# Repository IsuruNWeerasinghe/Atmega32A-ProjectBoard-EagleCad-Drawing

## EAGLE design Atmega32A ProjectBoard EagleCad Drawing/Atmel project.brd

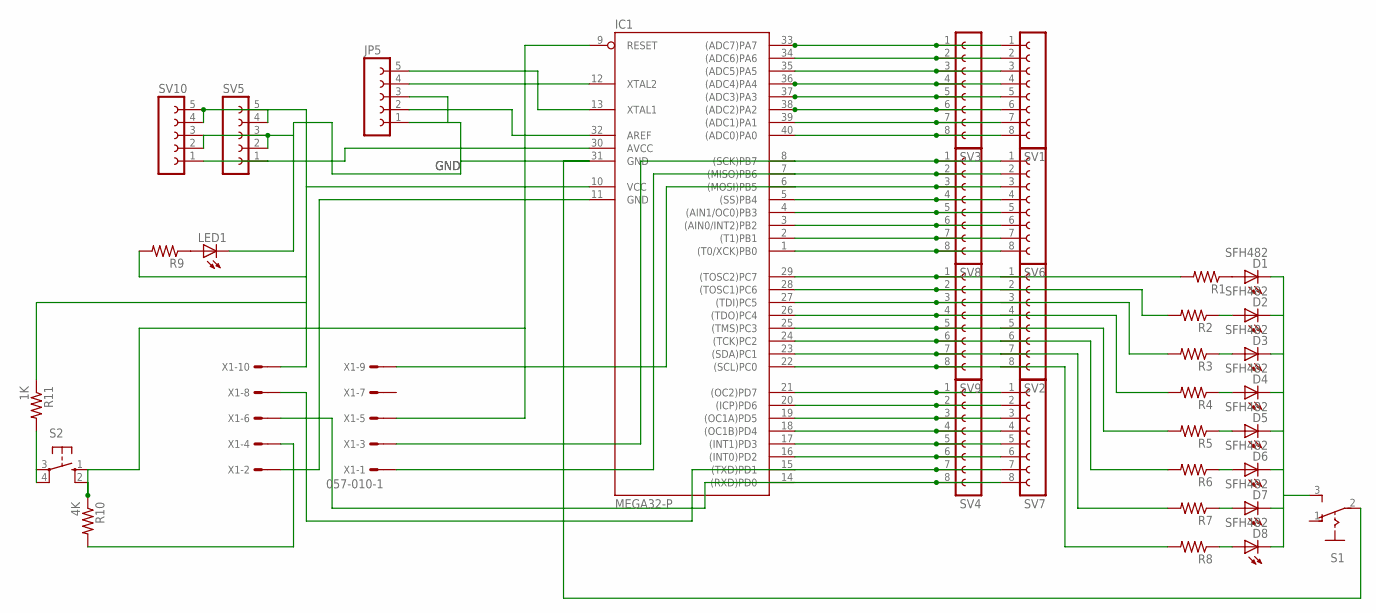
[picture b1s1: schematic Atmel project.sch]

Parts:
D1, D2, D3, D4, D5, D6, D7, D8: SFH482
IC1: MEGA32-P; DIL40
JP5: FE05-1
LED1: LED3MM
R1, R2, R3, R4, R5, R6, R7, R8, R9: R-US_0204/7; 0204/7
R10: 4K; 0204/7
R11: 1K; 0204/7
S1: 255SB
S2: 10-XX; B3F-10XX
SV1, SV2, SV3, SV4, SV6, SV7, SV8, SV9: FE08-1; FE08
SV5, SV10: FE05-1
X1: 057-010-1

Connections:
GND: IC1.11 (GND), IC1.31 (GND), JP5.1, JP5.3, LED1.K (C), R10.2, S1.2, SV5.2, SV5.3, SV10.2, SV10.3, X1.2, X1.4
unnamed: IC1.40 ((ADC0)PA0), SV1.8, SV3.8
unnamed: IC1.39 ((ADC1)PA1), SV1.7, SV3.7
unnamed: IC1.38 ((ADC2)PA2), SV1.6, SV3.6
unnamed: IC1.37 ((ADC3)PA3), SV1.5, SV3.5
unnamed: IC1.36 ((ADC4)PA4), SV1.4, SV3.4
unnamed: IC1.35 ((ADC5)PA5), SV1.3, SV3.3
unnamed: IC1.34 ((ADC6)PA6), SV1.2, SV3.2
unnamed: IC1.33 ((ADC7)PA7), SV1.1, SV3.1
unnamed: IC1.8 ((SCK)PB7), SV6.1, SV8.1, X1.3
unnamed: IC1.7 ((MISO)PB6), SV6.2, SV8.2, X1.1
unnamed: IC1.12 (XTAL2), JP5.4
unnamed: IC1.5 ((SS)PB4), SV6.4, SV8.4
unnamed: IC1.4 ((AIN1/OC0)PB3), SV6.5, SV8.5
unnamed: IC1.3 ((AIN0/INT2)PB2), SV6.6, SV8.6
unnamed: IC1.2 ((T1)PB1), SV6.7, SV8.7
unnamed: IC1.1 ((T0/XCK)PB0), SV6.8, SV8.8
unnamed: IC1.29 ((TOSC2)PC7), R1.2, SV2.1, SV9.1
unnamed: IC1.28 ((TOSC1)PC6), R2.2, SV2.2, SV9.2
unnamed: IC1.27 ((TDI)PC5), R3.2, SV2.3, SV9.3
unnamed: D1.K (C), D2.K (C), D3.K (C), D4.K (C), D5.K (C), D6.K (C), D7.K (C), D8.K (C), S1.3 (S)
unnamed: IC1.30 (AVCC), SV5.1, SV10.1
unnamed: IC1.32 (AREF), JP5.2
unnamed: IC1.24 ((TCK)PC2), R6.2, SV2.6, SV9.6
unnamed: IC1.22 ((SCL)PC0), R8.2, SV2.8, SV9.8
unnamed: IC1.21 ((OC2)PD7), SV4.1, SV7.1
unnamed: IC1.20 ((ICP)PD6), SV4.2, SV7.2
unnamed: IC1.19 ((OC1A)PD5), SV4.3, SV7.3
unnamed: IC1.18 ((OC1B)PD4), SV4.4, SV7.4
unnamed: IC1.17 ((INT1)PD3), SV4.5, SV7.5
unnamed: IC1.16 ((INT0)PD2), SV4.6, SV7.6
unnamed: IC1.15 ((TXD)PD1), SV4.7, SV7.7, X1.8
unnamed: IC1.14 ((RXD)PD0), SV4.8, SV7.8, X1.6
unnamed: IC1.25 ((TMS)PC3), R5.2, SV2.5, SV9.5
unnamed: LED1.A, R9.1
unnamed: D1.A, R1.1
unnamed: D2.A, R2.1
unnamed: D3.A, R3.1
unnamed: D4.A, R4.1
unnamed: D5.A, R5.1
unnamed: D6.A, R6.1
unnamed: D7.A, R7.1
unnamed: D8.A, R8.1
unnamed: IC1.9 (RESET), R10.1, S2.1 (S), S2.2 (S1), X1.5
unnamed: IC1.23 ((SDA)PC1), R7.2, SV2.7, SV9.7
unnamed: IC1.26 ((TDO)PC4), R4.2, SV2.4, SV9.4
unnamed: IC1.13 (XTAL1), JP5.5
unnamed: IC1.6 ((MOSI)PB5), SV6.3, SV8.3, X1.9
unnamed: IC1.10 (VCC), R9.2, R11.1, SV5.4, SV5.5, SV10.4, SV10.5, X1.10
unnamed: R11.2, S2.3, S2.4 (P1)

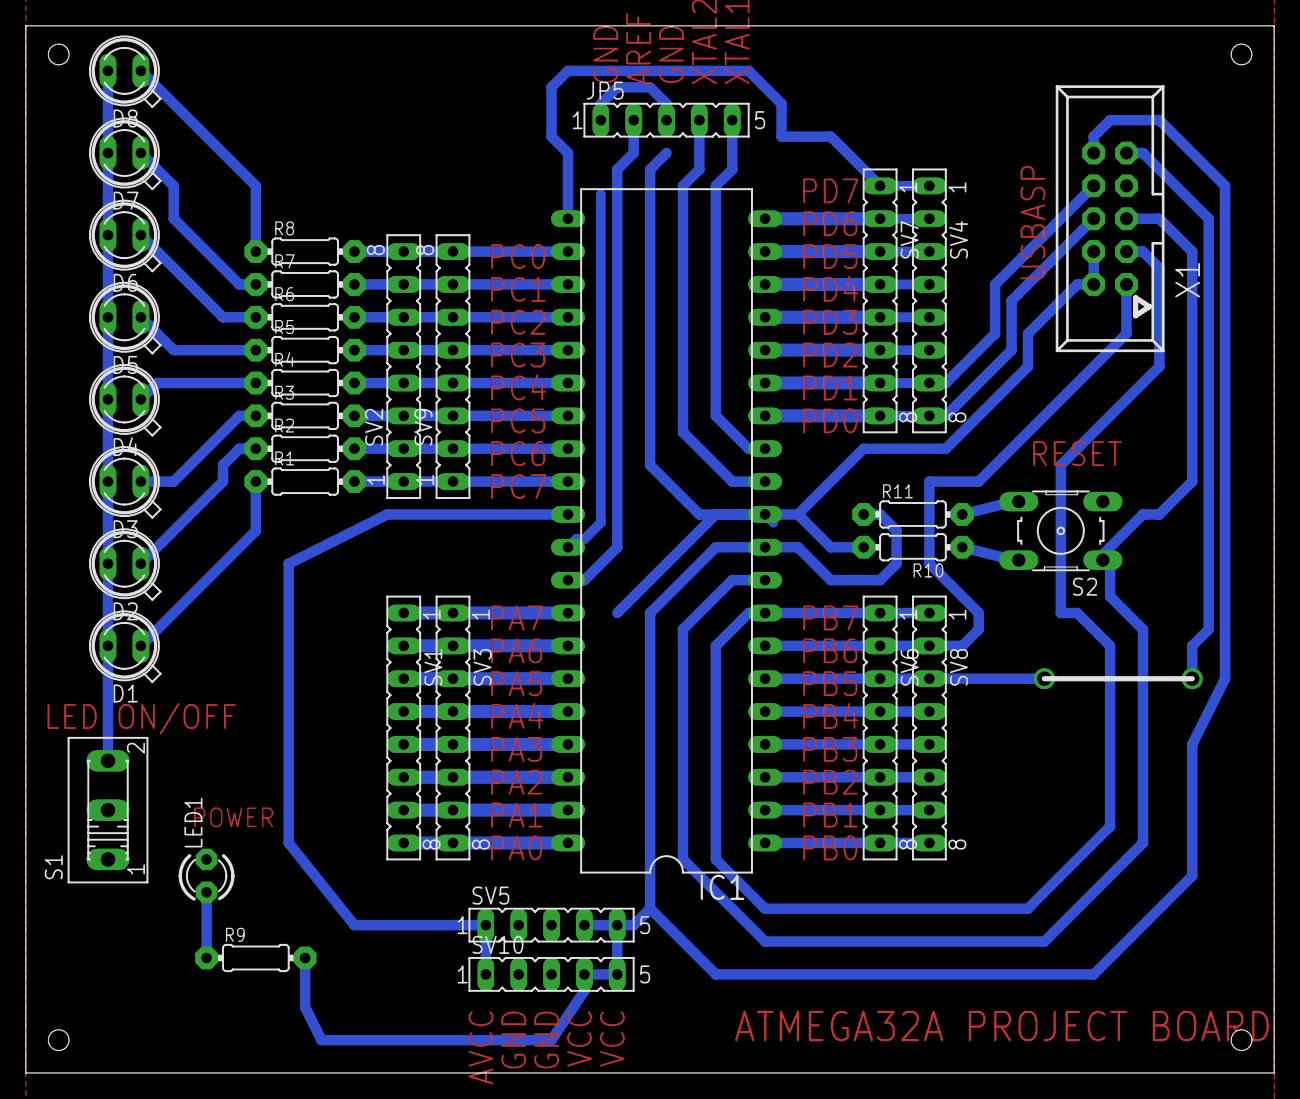
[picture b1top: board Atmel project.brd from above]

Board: 2 copper layers, 96.5 x 81.0 mm, 35 parts (0 on the bottom side), 50 nets.
